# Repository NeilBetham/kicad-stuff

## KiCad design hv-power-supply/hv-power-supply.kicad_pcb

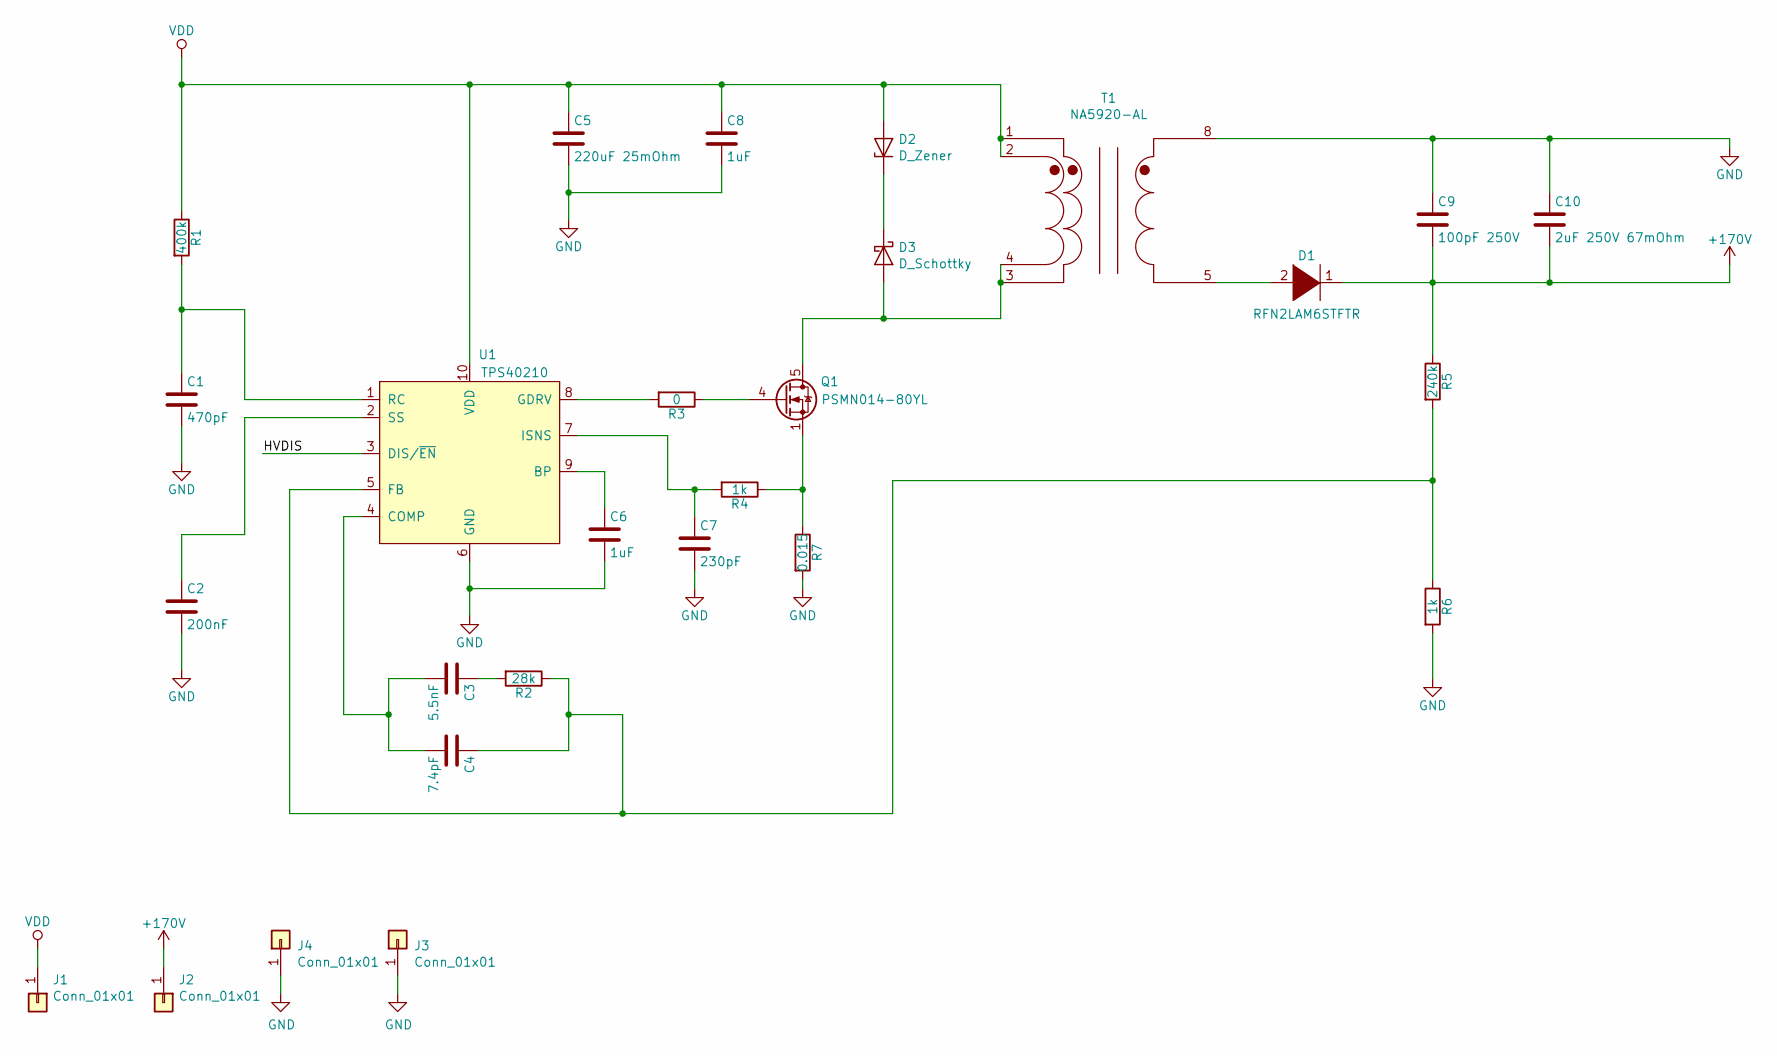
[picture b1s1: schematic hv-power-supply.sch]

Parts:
C1: 470pF; C_0805_2012Metric_Pad1.15x1.40mm_HandSolder
C2: 200nF; C_0805_2012Metric_Pad1.15x1.40mm_HandSolder
C3: 5.5nF; C_0805_2012Metric_Pad1.15x1.40mm_HandSolder
C4: 7.4pF; C_0805_2012Metric_Pad1.15x1.40mm_HandSolder
C5: 220uF 25mOhm; C_2816_7142Metric_Pad3.20x4.45mm_HandSolder; Part Number TPME227K016R0025
C6, C8: 1uF; C_0805_2012Metric_Pad1.15x1.40mm_HandSolder
C7: 230pF; C_0805_2012Metric_Pad1.15x1.40mm_HandSolder
C9: 100pF 250V; C_0805_2012Metric_Pad1.15x1.40mm_HandSolder
C10: 2uF 250V 67mOhm; C_2220_5650Metric_Pad1.97x5.40mm_HandSolder
D1: RFN2LAM6STFTR; D_SOD-123
D2: D_Zener; D_SOD-123; Part Number BZT52-B75J
D3: D_Schottky; D_1206_3216Metric_Castellated; Part Number CD1206-B2100
J1, J2, J3, J4: Conn_01x01; Pin_D1.3mm_L11.0mm
Q1: PSMN014-80YL; LFPAK56
R1: 400k; R_0805_2012Metric_Pad1.15x1.40mm_HandSolder
R2: 28k; R_0805_2012Metric_Pad1.15x1.40mm_HandSolder
R3: 0; R_0805_2012Metric_Pad1.15x1.40mm_HandSolder
R4, R6: 1k; R_0805_2012Metric_Pad1.15x1.40mm_HandSolder
R5: 240k; R_0805_2012Metric_Pad1.15x1.40mm_HandSolder
R7: 0.015; R_GMR_100
T1: NA5920-AL; NA6252-AL
U1: TPS40210; MSOP-10-1EP_3x3mm_P0.5mm_EP1.68x1.88mm

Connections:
+170V: C9.2, C10.2, D1.1 (A), J2.1, R5.1
/HVDIS: U1.3 (DIS/~EN)
GND: C1.2, C2.2, C5.2, C6.2, C7.2, C8.2, C9.1, C10.1, J3.1, J4.1, R6.2, R7.2, T1.8, U1.6 (GND), U1.11 (GND)
unnamed: C1.1, R1.2, U1.1 (RC)
unnamed: C2.1, U1.2 (SS)
unnamed: C3.1, R2.2
unnamed: C3.2, C4.2, U1.4 (COMP)
unnamed: C4.1, R2.1, R5.2, R6.1, U1.5 (FB)
unnamed: C6.1, U1.9 (BP)
unnamed: C7.1, R4.2, U1.7 (ISNS)
unnamed: D1.2 (K), T1.5
unnamed: D2.1 (K), D3.1 (K)
unnamed: D3.2 (A), Q1.5 (D), T1.3, T1.4
unnamed: Q1.1 (S), Q1.2 (S), Q1.3 (S), R4.1, R7.1
unnamed: Q1.4 (G), R3.1
unnamed: R3.2, U1.8 (GDRV)
VDD: C5.1, C8.1, D2.2 (A), J1.1, R1.1, T1.1, T1.2, U1.10 (VDD)

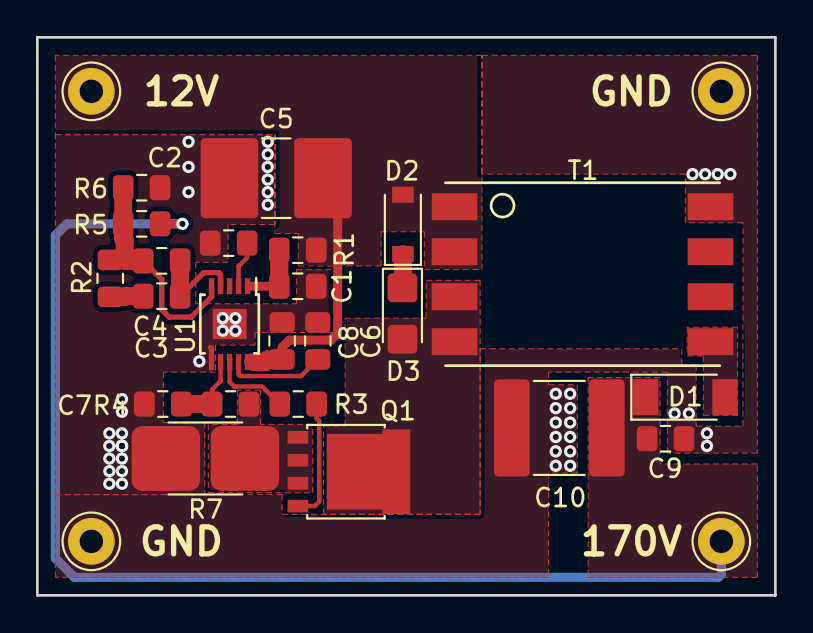
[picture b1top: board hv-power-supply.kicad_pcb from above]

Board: 2 copper layers, 41.0 x 31.0 mm, 27 parts (0 on the bottom side), 16 nets.

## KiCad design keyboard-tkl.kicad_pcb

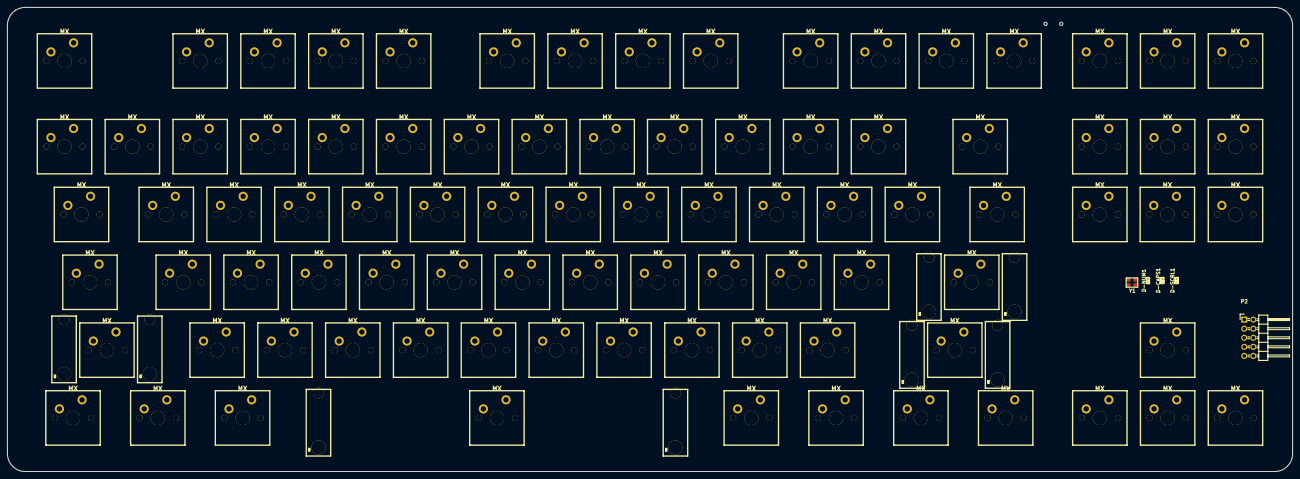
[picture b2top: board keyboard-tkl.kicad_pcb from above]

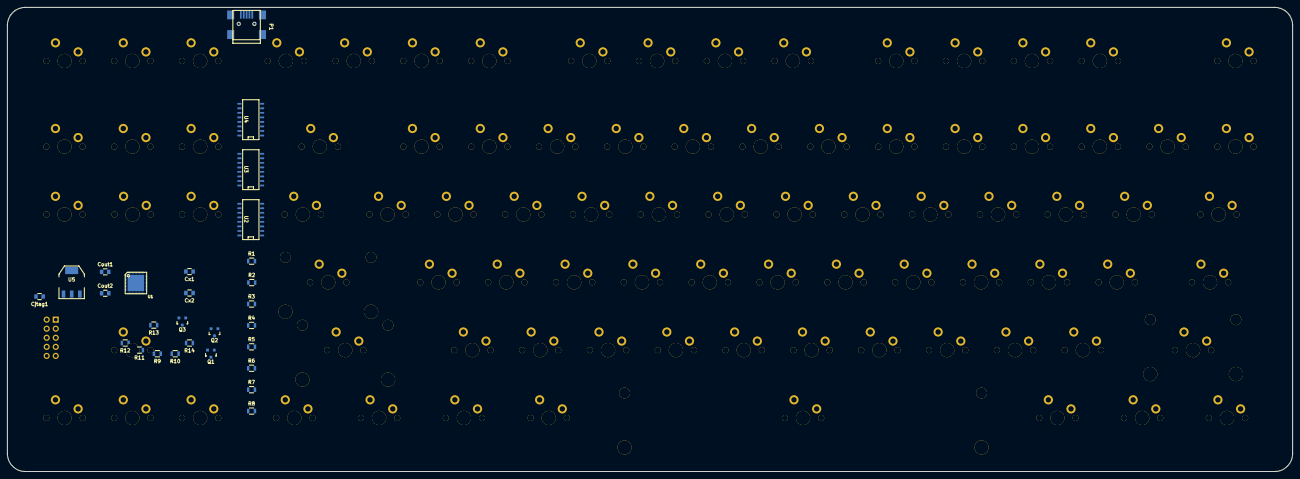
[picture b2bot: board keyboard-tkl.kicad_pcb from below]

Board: 4 copper layers, 360.0 x 130.0 mm, 128 parts (28 on the bottom side), 54 nets, no tracks yet.

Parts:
Cjtag1: 100nF; C_0805
Cout1: 470pF; C_0805
Cout2: 2.2uF; C_0805
Cx1, Cx2: 22pF; C_0805
D-CAPS1: LED; LED-0603
D-NUM1: LED; LED-0603
D-SCRL1: LED; LED-0603
P1: USB_OTG; USB_Mini-B
P2: JTAG; Pin_Header_Angled_2x05
Q1, Q2, Q3: Q_NMOS_GSD; SOT-23
R1, R2: 39; R_0805
R3, R4, R5, R6, R7, R8, R9: 10k; R_0805
R10, R12, R14: 400; R_0805
R11, R13: 10K; R_0805
SW1, SW2, SW3, SW4, SW5, SW6, SW7, SW8: MX; MXST
SW-0, SW-1, SW-2, SW-3, SW-4, SW-5, SW-6, SW-7, SW-8, SW-9, SW-.1: MX; MX1A
SW-'1: MX; MX1A
SW-,1: MX; MX1A
SW--1: MX; MX1A
SW-/1: MX; MX1A
SW-;1: MX; MX1A
SW-=1: MX; MX1A
SW-A1: MX; MX1A
SW-ALT1: MX; MX1A
SW-B1: MX; MX1A
SW-BK-SPC1: MX; MX1A
SW-C1: MX; MX1A
SW-CAPS1: MX; MX1A
SW-CTRL1, SW-CTRL2: MX; MX1A
SW-D1: MX; MX1A
SW-DEL1: MX; MX1A
SW-DOWN1: MX; MX1A
SW-E1: MX; MX1A
SW-END1: MX; MX1A
SW-ESC1: MX; MX1A
SW-F1, SW-F2, SW-F3, SW-F4, SW-F5, SW-F6, SW-F7, SW-F8, SW-F9, SW-F10, SW-F11, SW-F12, SW-F13: MX; MX1A
SW-FN1: MX; MX1A
SW-G1: MX; MX1A
SW-H1: MX; MX1A
SW-HOME1: MX; MX1A
SW-I1: MX; MX1A
SW-INS1: MX; MX1A
SW-J1: MX; MX1A
SW-K1: MX; MX1A
SW-L1: MX; MX1A
SW-LEFT1: MX; MX1A
SW-M1: MX; MX1A
SW-MENU1: MX; MX1A
SW-N1: MX; MX1A
SW-O1: MX; MX1A
SW-OS1, SW-OS2: MX; MX1A
SW-P1: MX; MX1A
SW-PAUSE1: MX; MX1A
SW-PG-DWN1: MX; MX1A
SW-PGUP1: MX; MX1A
SW-PRINT1: MX; MX1A
SW-Q1: MX; MX1A
SW-R1: MX; MX1A
SW-RET1: MX; MX1A
SW-RIGHT1: MX; MX1A
SW-S1: MX; MX1A
SW-SCL-LOCK1: MX; MX1A
SW-SHIFT1, SW-SHIFT2: MX; MX1A
SW-SPACE1: MX; MX1A
SW-T1: MX; MX1A
SW-TAB1: MX; MX1A
SW-U1: MX; MX1A
SW-UP1: MX; MX1A
SW-V1: MX; MX1A
SW-W1: MX; MX1A
SW-X1: MX; MX1A
SW-Y1: MX; MX1A
SW-Z1: MX; MX1A
SW-[1: MX; MX1A
SW-\1: MX; MX1A
SW-]1: MX; MX1A
SW-`1: MX; MX1A
U1: AT32UC3B1512; QFN48+1
U2, U3, U4: 74HC595; SO-16-N
U5: LD1117S33CTR; SOT-223
Y1: 12MHz; crystal_FA238-TSX3225

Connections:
+5V: D-CAPS1.2, D-NUM1.2, D-SCRL1.2, P1.1, U1.40, U5.3
/CAPS: Q1.1, R9.1, U1.25
/COL1: SW-CAPS1.1, SW-CTRL1.1, SW-ESC1.1, SW-SHIFT1.1, SW-TAB1.1, SW-`1.1, U2.15
/COL2: SW-1.1, SW-A1.1, SW-ALT1.1, SW-Q1.1, SW-Z1.1, U2.1
/COL3: SW-2.1, SW-F1.1, SW-OS1.1, SW-S1.1, SW-W1.1, SW-X1.1, U2.2
/COL4: SW-3.1, SW-C1.1, SW-D1.1, SW-E1.1, SW-F2.1, U2.3
/COL5: SW-4.1, SW-F3.1, SW-F13.1, SW-R1.1, SW-V1.1, U2.4
/COL6: SW-5.1, SW-B1.1, SW-F4.1, SW-G1.1, SW-SPACE1.1, SW-T1.1, U2.5
/COL7: SW-6.1, SW-F5.1, SW-H1.1, SW-N1.1, SW-Y1.1, U2.6
/COL8: SW-7.1, SW-F6.1, SW-J1.1, SW-M1.1, SW-U1.1, U2.7
/COL9: SW-8.1, SW-,1.1, SW-F7.1, SW-I1.1, SW-K1.1, U3.15
/COL10: SW-9.1, SW-.1.1, SW-F8.1, SW-L1.1, SW-O1.1, SW-OS2.1, U3.1
/COL11: SW-0.1, SW-/1.1, SW-;1.1, SW-F9.1, SW-FN1.1, SW-P1.1, U3.2
/COL12: SW-'1.1, SW--1.1, SW-F10.1, SW-[1.1, U3.3
/COL13: SW-=1.1, SW-F11.1, SW-MENU1.1, SW-RET1.1, SW-SHIFT2.1, SW-]1.1, U3.4
/COL14: SW-BK-SPC1.1, SW-CTRL2.1, SW-F12.1, SW-\1.1, U3.5
/COL15: SW-DEL1.1, SW-INS1.1, SW-LEFT1.1, SW-PRINT1.1, U3.6
/COL16: SW-DOWN1.1, SW-END1.1, SW-HOME1.1, SW-SCL-LOCK1.1, SW-UP1.1, U3.7
/COL17: SW-PAUSE1.1, SW-PG-DWN1.1, SW-PGUP1.1, SW-RIGHT1.1, U4.15
/NUM: Q3.1, R13.1, U1.27
/RESET: P2.6, U1.47
/ROW1: R3.1, SW-ESC1.2, SW-F1.2, SW-F2.2, SW-F3.2, SW-F4.2, SW-F5.2, SW-F6.2, SW-F7.2, SW-F8.2, SW-F9.2, SW-F10.2, SW-F11.2, SW-F12.2, SW-PAUSE1.2, SW-PRINT1.2, SW-SCL-LOCK1.2, U1.7
/ROW2: R4.1, SW-0.2, SW-1.2, SW-2.2, SW-3.2, SW-4.2, SW-5.2, SW-6.2, SW-7.2, SW-8.2, SW-9.2, SW--1.2, SW-=1.2, SW-BK-SPC1.2, SW-HOME1.2, SW-INS1.2, SW-PGUP1.2, SW-`1.2, U1.8
/ROW3: R5.1, SW-DEL1.2, SW-E1.2, SW-END1.2, SW-I1.2, SW-O1.2, SW-P1.2, SW-PG-DWN1.2, SW-Q1.2, SW-R1.2, SW-T1.2, SW-TAB1.2, SW-U1.2, SW-W1.2, SW-Y1.2, SW-[1.2, SW-\1.2, SW-]1.2, U1.9
/ROW4: R6.1, SW-'1.2, SW-;1.2, SW-A1.2, SW-CAPS1.2, SW-D1.2, SW-F13.2, SW-G1.2, SW-H1.2, SW-J1.2, SW-K1.2, SW-L1.2, SW-RET1.2, SW-S1.2, U1.10
/ROW5: R7.1, SW-,1.2, SW-.1.2, SW-/1.2, SW-B1.2, SW-C1.2, SW-M1.2, SW-N1.2, SW-SHIFT1.2, SW-SHIFT2.2, SW-UP1.2, SW-V1.2, SW-X1.2, SW-Z1.2, U1.11
/ROW6: R8.1, SW-ALT1.2, SW-CTRL1.2, SW-CTRL2.2, SW-DOWN1.2, SW-FN1.2, SW-LEFT1.2, SW-MENU1.2, SW-OS1.2, SW-OS2.2, SW-RIGHT1.2, SW-SPACE1.2, U1.12
/SCRL: Q2.1, R11.1, U1.26
/TCK: P2.1, U1.2
/TDI: P2.9, U1.3
/TDO: P2.3, U1.4
/TMS: P2.5, U1.5
/USB_DM: P1.3, R1.1
/USB_DP: P1.2, R2.1
/USB_ID: P1.4, U1.45
/VDDOUT: Cout1.1, Cout2.1, U1.6, U1.16, U1.18, U1.41, U1.42
/XIN: Cx1.2, U1.30, Y1.1
/XOUT: Cx2.2, U1.31, Y1.2
GND: Cjtag1.1, Cout1.2, Cout2.2, Cx1.1, Cx2.1, P1.5, P1.6, P2.2, P2.10, R3.2, R4.2, R5.2, R6.2, R7.2, R8.2, R9.2, R10.2, R11.2, R12.2, R13.2, R14.2, U1.1, U1.13, U1.19, U1.37, U2.8, U2.13, U3.8, U3.13, U4.8, U4.13, U5.1
unnamed: D-CAPS1.1, Q1.3
unnamed: D-NUM1.1, Q3.3
unnamed: D-SCRL1.1, Q2.3
unnamed: Q1.2, R10.1
unnamed: Q2.2, R12.1
unnamed: Q3.2, R14.1
unnamed: R1.2, U1.39
unnamed: R2.2, U1.38
unnamed: U1.20, U2.14
unnamed: U1.21, U2.11, U3.11, U4.11
unnamed: U1.22, U2.10, U3.10, U4.10
unnamed: U1.23, U2.12, U3.12, U4.12
unnamed: U2.9, U3.14
unnamed: U3.9, U4.14
VCC: Cjtag1.2, P2.4, U1.14, U1.15, U1.17, U1.24, U1.36, U1.48, U2.16, U3.16, U4.16, U5.2
